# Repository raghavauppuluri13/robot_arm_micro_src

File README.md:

# robot_arm_micro_src

Source files for robot arm project for ECE 362

[Project Video](https://www.youtube.com/watch?v=FccGxyFGFdw&list=PLnXxGWN1CH0dvdpDsjcVRisxLoUF9EFiQ&index=1)

## Arm Details

- 6 Hobby servos controlled with PWM (duty cycle corresponds to angle)
- [Servo 0-2 datasheet](https://components101.com/sites/default/files/component_datasheet/MG996R-Datasheet.pdf)
- [Servo 3 datasheet](http://www.ee.ic.ac.uk/pcheung/teaching/DE1_EE/stores/sg90_datasheet.pdf)
- [Servo 4-5](https://www.agf-rc.com/agfrc-digital-servo-b11dls-p1670802.html)

## System Overview

### Servo Comms

PWM/Timers/ADC

- Angle to PWM interface -> use Timers and DAC

Raghava

### LCD Display

- X, Y, Z Coordinates
- Top down view and side view
- Current state?
- Place a marker where objects are anticipated to be? (Would have to be input by user)
- If recording motions is added, add a timer to the screen and a red dot to indicate it is being recorded.

Kaden

### Keyboard control

GPIO

Map 6 keyboard keys to +- x/y/z steps 

Anyone, relatively easy
- Kaden is willing to do this as well

### Robot Stuff

Convert current position of gripper to joint angles (inverse kinematics). Need to use fixed point math. 

Raghava/Rohan

### Circuit Design

- Connect all servos in parallel to 5V/ground
- Connect servo data pins to respective STM32 pinouts

Rohit/Kaden

### Safety

- Establish joint limits and operating range, draw circle.
- Wired E-stop connected to circuit to cut power

### Other Random Ideas/Notes if needed
- Automatic Advanced controls by way of keypad
- Extend the base to be the extent of the safety circle
- A way to record the robot arm's movements and store them for future use.
- Save automatic motions, possibly in an SD card.
- A default reset state for the arm
- Some way of telling the user the controls if advanced functions are added.
- Pick up stacks of boxes and keep it stable.
- Have a continuous move object mode, where when a box is placed on top of a sensor, the arm automatically moves it.

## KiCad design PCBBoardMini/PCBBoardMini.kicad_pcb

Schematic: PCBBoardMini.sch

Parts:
C1: 22 uF; C_0805_2012Metric_Pad1.18x1.45mm_HandSolder
C2, C4: 10 uF; C_0805_2012Metric_Pad1.18x1.45mm_HandSolder
C3: 0.1 uF; C_0805_2012Metric_Pad1.18x1.45mm_HandSolder
C5, C6, C7, C12: C_Small; C_0805_2012Metric_Pad1.18x1.45mm_HandSolder
D1: BAT60A; D_SOD-323
J1: AudioJack4; audioJack
R1: Device_R_US; R_0805_2012Metric_Pad1.20x1.40mm_HandSolder
R2: R_Small_US; R_0805_2012Metric_Pad1.20x1.40mm_HandSolder
RV1, RV2, RV3, RV4: R_POT_US; joysticks
SW1: Switch_SW_Push; nrstButton
U1, U2, U3, U8, U9, U10, U11, U12, U13: joystick_or_servo; joysticks
U4: programmerblock; programmerblockthing
U5: LD1117S33TR_SOT223; SOT-223-3_TabPin2
U6: STM32F091RCTx; LQFP-64_10x10mm_P0.5mm
U7: lcdscreen; lcd screen
U14: rx_tx; txrx

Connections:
+5V: C1.1, C12.1, U4.1, U5.3 (VI), U8.2, U9.2, U10.2, U11.2, U12.2, U13.2, U14.1, U14.4; also elsewhere on the board
GND: C1.2, C3.2, C4.2, C5.1, C6.2, C7.2, C12.2, J1.R2, R2.2, RV1.1, RV2.1, RV3.1, RV4.1, SW1.1, U1.3, U2.3, U3.3, U4.3, U5.1 (GND), U6.12 (VSSA), U6.18 (VSS), U6.31 (VSS), U6.47 (VSS), U6.63 (VSS), U7.2, U8.3, U9.3, U10.3, U11.3, U12.3, U13.3, U14.2, U14.5; also elsewhere on the board
unnamed: C2.1, U6.20 (PA4)
unnamed: C2.2, RV4.3
unnamed: C3.1, C4.1, C6.1, C7.1, D1.1 (K), R1.2, RV1.3, RV2.3, RV3.3, U1.2, U2.2, U3.2, U6.1 (VBAT), U6.13 (VDDA), U6.19 (VDD), U6.32 (VDD), U6.48 (VDDIO2), U6.64 (VDD), U7.1, U7.8
unnamed: C5.2, R1.1, SW1.2, U4.5, U6.7 (NRST)
unnamed: D1.2 (A), U5.2 (VO)
unnamed: J1.R1, J1.T, RV4.2
unnamed: R2.1, U6.60 (PF11)
unnamed: RV1.2, U6.11 (PC3)
unnamed: RV2.2, U6.24 (PC4)
unnamed: RV3.2, U6.25 (PC5)
unnamed: U1.1, U6.8 (PC0)
unnamed: U2.1, U6.9 (PC1)
unnamed: U3.1, U6.10 (PC2)
unnamed: U4.2, U6.49 (PA14)
unnamed: U4.4, U6.46 (PA13)
unnamed: U6.17 (PA3), U8.1
unnamed: U6.21 (PA5), U7.7
unnamed: U6.23 (PA7), U7.6
unnamed: U6.27 (PB1), U9.1
unnamed: U6.30 (PB11), U7.4
unnamed: U6.35 (PB14), U7.5
unnamed: U6.61 (PB8), U7.3
unnamed: U6.56 (PB4), U10.1
unnamed: U6.57 (PB5), U11.1
unnamed: U6.15 (PA1), U12.1
unnamed: U6.16 (PA2), U13.1
unnamed: U6.29 (PB10), U14.3

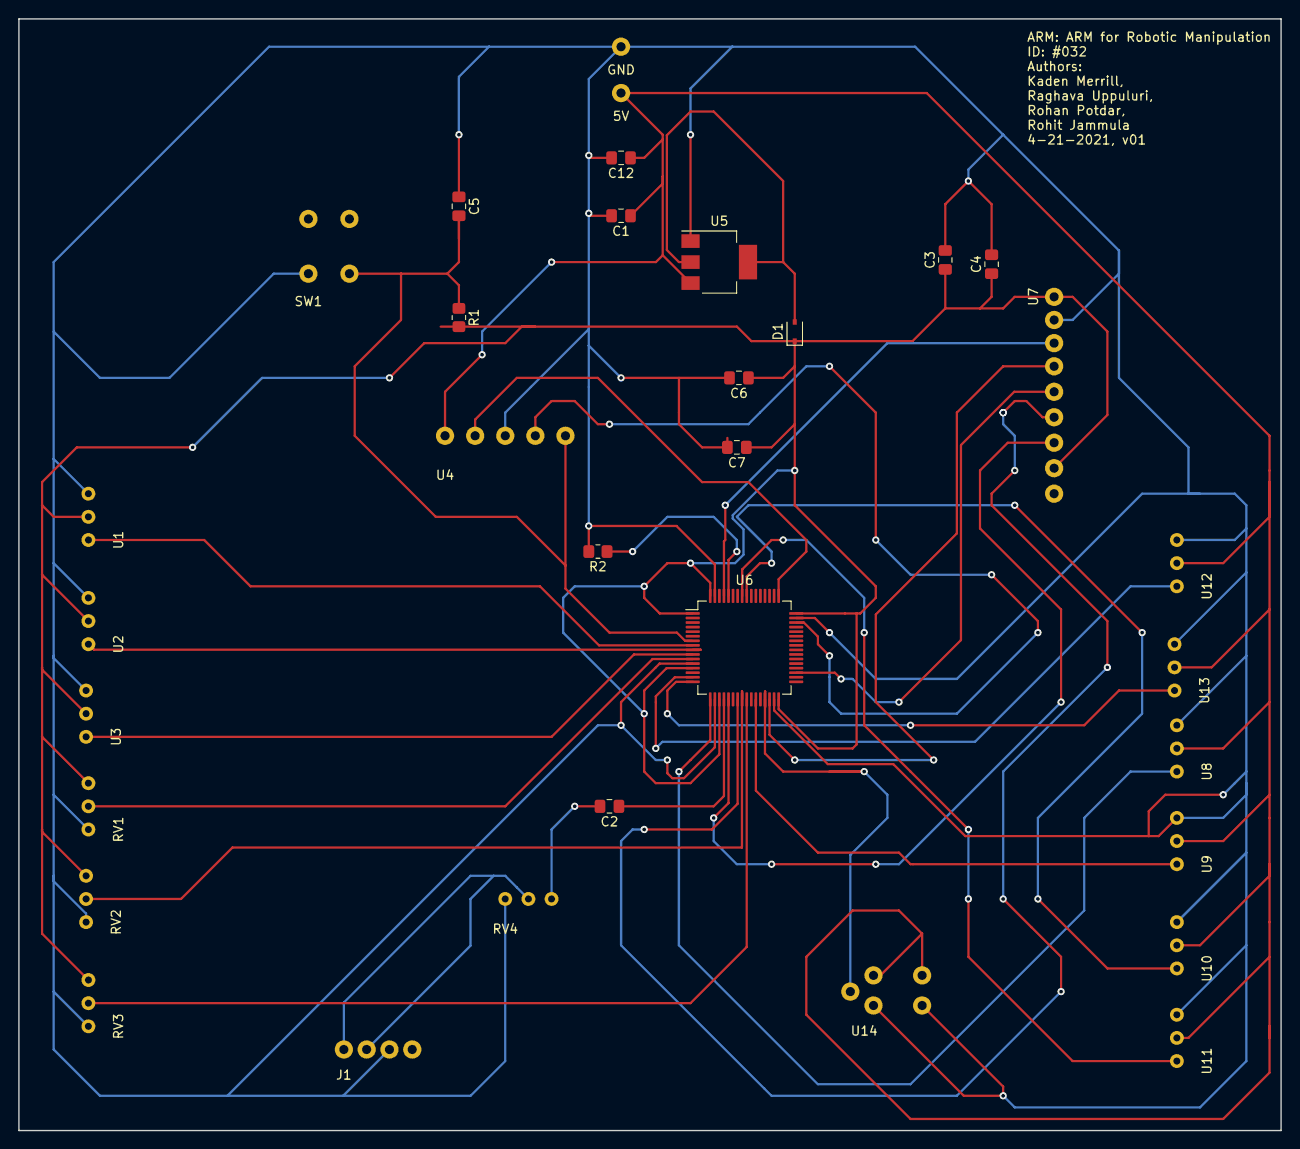
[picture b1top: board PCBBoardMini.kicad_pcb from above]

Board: 2 copper layers, 138.4 x 121.9 mm, 33 parts (0 on the bottom side), 29 nets.

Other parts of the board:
5V: pwrgnd
GND: pwrgnd

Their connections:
+5V: 5V.1; also elsewhere on the board
GND: GND.1; also elsewhere on the board

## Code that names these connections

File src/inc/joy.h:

#ifndef __JOY_H__
#define __JOY_H__
#include "stm32f0xx.h"

#define BCSIZE 32
#define JOY_CNT 6
#define UPPER_JOY_MID 2300
#define LOWER_JOY_MID 1500

/*
  - Data Pinouts:
    - 2 Joysticks (one axis will be unused):
        - X-axis, PC0, ADC_IN10, JOY ID 0
        - Y-axis, PC1, ADC_IN11, JOY ID 1
        - Z-axis, PC2, ADC_IN12, JOY ID 2
    - 3 Potentiometers (10kohm pots):
        - Wrist-roll, PC3, ADC_IN13, JOY ID 3
        - Wrist-pitch, PC4, ADC_IN14, JOY ID 4
        - Gripper, PC5, ADC_IN15, JOY ID 5
 */

struct JoySpec {
    // GPIOC
    uint8_t pin;
    // channel
    uint8_t ch;
};

static const struct JoySpec joy_specs[JOY_CNT] = {
  { .pin = 0, .ch = 10},
  { .pin = 1, .ch = 11},
  { .pin = 2, .ch = 12},
  { .pin = 3, .ch = 13},
  { .pin = 4, .ch = 14},
  { .pin = 5, .ch = 15}
};

struct Joy {
    // output of boxcar value
    int32_t val;
    // boxcar averaging
    int bcsum;
    int boxcar[BCSIZE];
    int bcn;
};


void init_joys();
void start_joys(void);
void init_tim15();

#endif

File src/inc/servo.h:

#include "stm32f0xx.h"

#ifndef __SERVO_H__
#define __SERVO_H__

// PWM period=20ms
#define PWM_PSC 16
#define PWM_ARR 60000

#define MIN_DEG 0
#define MAX_DEG 180

// 0.0272 duty cycle - 0 deg
// min pulse width = 544ns
#define MIN_CCR 1632
// 90 deg
#define MID_CCR 4416
// 0.12s duty cycle - 180 deg
// max pulse width = 2400ns
#define MAX_CCR 7200
#define SERVO_CNT 6

/* Valid servo pin map:
 * TIM2_CH2: PA1, AF2  SERVO ID #0
 * TIM2_CH3: PA2, AF2, SERVO ID #1
 * TIM2_CH4: PA3, AF2, SERVO ID #2
 *
 * TIM3_CH4: PB1, AF1, SERVO ID #3
 * TIM3_CH1: PB4, AF1, SERVO ID #4
 * TIM3_CH2: PB5, AF1, SERVO ID #5
 */
struct ServoSpec {
    uint8_t pin;
    TIM_TypeDef* tim;
    GPIO_TypeDef* gpio;
    uint8_t af;
    __IO uint32_t* ccmr;
    __IO uint32_t* ccr;
    uint16_t mode_preload;
    uint16_t ccer_en;
    uint8_t max_ang;
    uint8_t init_ang;
    uint8_t min_ang;
};

static const struct ServoSpec srv_specs[SERVO_CNT] = {
        /****************************** ID 0 **********************************/
        { .pin = 1, .gpio = GPIOA, .tim=TIM2, .af = 2,
          .ccmr = &(TIM2->CCMR1), .ccr = &(TIM2->CCR2), .ccer_en = TIM_CCER_CC2E,
          .mode_preload = TIM_CCMR1_OC2M_2 | TIM_CCMR1_OC2M_1| TIM_CCMR1_OC2PE,
          .min_ang = 0, .max_ang = 180, .init_ang = 90
        },
        /****************************** ID 1 **********************************/
        { .pin = 2, .gpio = GPIOA, .tim=TIM2, .af = 2,
          .ccmr = &(TIM2->CCMR2), .ccr = &(TIM2->CCR3),.ccer_en = TIM_CCER_CC3E,
          .mode_preload = TIM_CCMR2_OC3M_2 | TIM_CCMR2_OC3M_1 | TIM_CCMR2_OC3PE,
          .min_ang = 0, .max_ang = 180, .init_ang = 90
        },
        /****************************** ID 2 **********************************/
        { .pin = 3, .gpio = GPIOA, .tim=TIM2, .af = 2,
          .ccmr = &(TIM2->CCMR2), .ccr = &(TIM2->CCR4),.ccer_en = TIM_CCER_CC4E,
          .mode_preload = TIM_CCMR2_OC4M_2 | TIM_CCMR2_OC4M_1 | TIM_CCMR2_OC4PE,
          .min_ang = 75, .max_ang = 105, .init_ang = 90
        },
        /****************************** ID 3 **********************************/
        { .pin = 1, .gpio = GPIOB, .tim=TIM3, .af = 1,
          .ccmr = &(TIM3->CCMR2), .ccr = &(TIM3->CCR4),.ccer_en = TIM_CCER_CC4E,
          .mode_preload = TIM_CCMR2_OC4M_2 | TIM_CCMR2_OC4M_1 | TIM_CCMR2_OC4PE,
          .min_ang = 15, .max_ang = 160, .init_ang = 90
        },
        /****************************** ID 4 **********************************/
        { .pin = 4, .gpio = GPIOB, .tim=TIM3, .af = 1,
          .ccmr = &(TIM3->CCMR1), .ccr = &(TIM3->CCR1),.ccer_en = TIM_CCER_CC1E,
          .mode_preload = TIM_CCMR1_OC1M_2 | TIM_CCMR1_OC1M_1 | TIM_CCMR1_OC1PE,
          .min_ang = 0, .max_ang = 180, .init_ang = 90
        },
        /****************************** ID 5 **********************************/
        { .pin = 5, .gpio = GPIOB, .tim=TIM3, .af = 1,
          .ccmr = &(TIM3->CCMR1), .ccr = &(TIM3->CCR2),.ccer_en = TIM_CCER_CC2E,
          .mode_preload = TIM_CCMR1_OC2M_2 | TIM_CCMR1_OC2M_1 | TIM_CCMR1_OC2PE,
          .min_ang = 0, .max_ang = 180, .init_ang = 100
        },
};

// servo and pwm inits
void pwm_gpio_init();

void servo_init(uint8_t id);

// clamps a value
void clamp(float* val, int max, int min);

// writes a degree value to a servo
void servo_write(uint8_t id, float deg);

// maps a degree value to CCR value
static uint32_t map(uint32_t in, uint32_t from_high, uint32_t from_low,
                                  uint32_t to_high,   uint32_t to_low);

#endif

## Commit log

2022-04-15 menu part 1
2022-04-17 servo, joystick, and serial code
2022-04-17 fixed bugs
2022-04-18 tested servos, they work
2022-04-18 serial debugger and potentiometer works
2022-04-18 joystick tests, works well
2022-04-18 added servo tests, now has smooth motion
2022-04-22 break beam sensor score counter works
2022-04-22 added IK code
2022-04-22 kicad files
2022-04-25 working IK, added/passedrobot integration tests, thus robot arm control system basically works
2022-04-25 param updates
2022-04-25 config changes
2022-04-25 midi and display works
2022-04-25 all components are working, was able to play 3 straight games
2022-04-28 start/stop for robot arm during/after game
2022-04-28 bug fixes
2022-10-13 Update README.md Update README.md servo, joystick, and serial code
    fixed bugs
    tested servos, they work
    serial debugger and potentiometer works
    joystick tests, works well
    added servo tests, now has smooth motion
    break beam sensor score counter works
